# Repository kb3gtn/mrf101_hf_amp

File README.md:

# MRF101 HF AMP design

## Introduction
This repository contains multiple circuits board designs for a 100W HF Amp using a single MRF-101A transistor.   This design is based on a design by HF5L.   This design operates with a 48V Nominal supply at around 3.5 Amps of current.

Input match is good from 160M -> 6M band (1.8M -> 54 MHz).   Device has a between 16 -> 20 dB of gain depending on frequency.

## KICAD design files
The Main Amp Deck consists of the MRF101 transistor and input/output matching circuitry.
This can be found in the /Amp_Main_Deck/kicad folder in this repository.   The amplifier deck requires output filtering to remove odd harmonics produced by the Class AB amp.   The filters are selected per band of operation.

## Powering the Amp
The concept to power the amplifier design is to use 2 6S LiPo batteries in series.  This will provide a 44 -> 52v operating range.  Current plan is to use RC batteries and off the shelf chargers for portable operation.

## TODO
Design some BFP filters for each of the HF Amateur Radio bands, will need to develop a switch bank to select which filter should be in line.   Using BPF because this will provide some selectivity and limit the amount of bandwidth being sampled for a SDR receiver architecture.

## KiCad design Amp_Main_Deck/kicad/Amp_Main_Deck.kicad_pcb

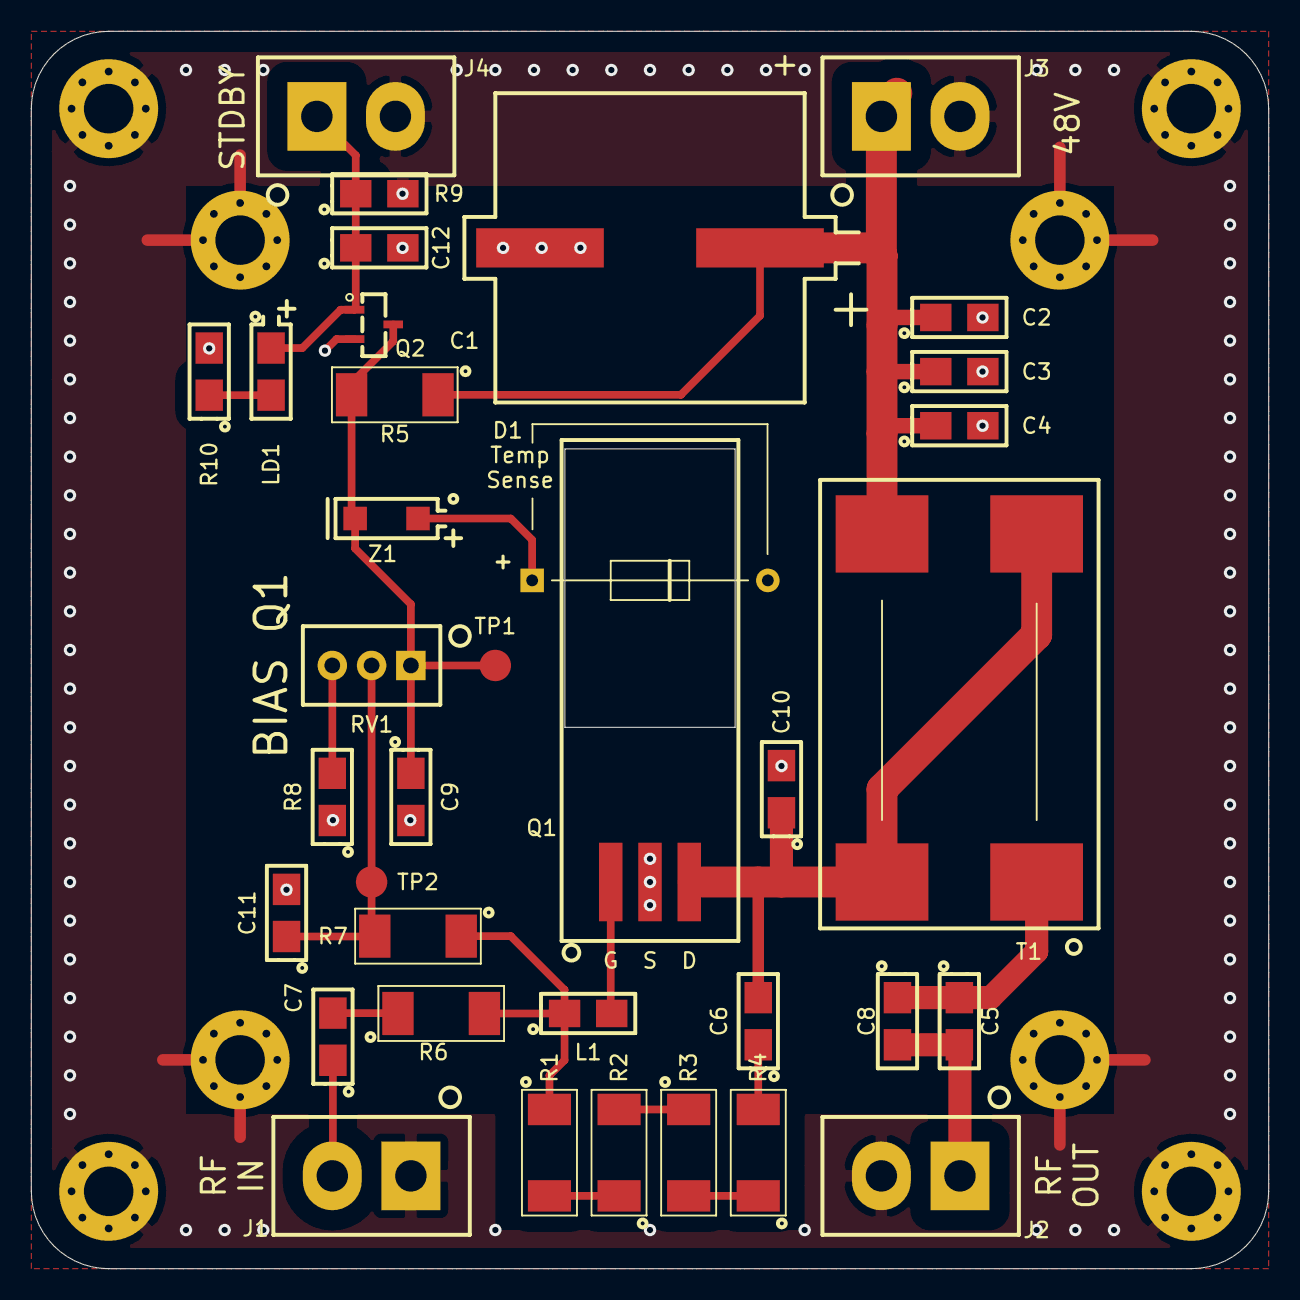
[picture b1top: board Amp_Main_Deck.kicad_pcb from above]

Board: 2 copper layers, 80.0 x 80.0 mm, 44 parts (0 on the bottom side), 19 nets.

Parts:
C1: CP; UCZ1K331MNQ1MS
C2, C3, C4, C5, C6, C7, C8, C9, C10, C11, C12: C; 0805_handsolder
D1: Diode_Generic; Diode_600mil
H1, H2, H3, H4, H5, H6, H7, H8: MountingHole_Pad; MountingHole_3.2mm_M3_Pad_Via
J1, J2, J3, J4: TermBlock_2pin; TermBlock_200mil_2pin
L1: L; 0805_handsolder
LD1: Diode_LED; 0805_handsolder_Pol
Q1: MRF101A; MRF-101AN_SM
Q2: 2N7002; SOT-23
R1, R2, R3, R4, R5, R6, R7: R; 2010_handsolder
R8, R9, R10: R; 0805_handsolder
RV1: Trim_POT; 3296W-1-103LF
T1: CMC; 744851330
TP1, TP2: SMD_TP
Z1: Diode_Zener; SOD123

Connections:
/48v: C1.1, C2.1, C3.1, C4.1, J3.1, R5.1, T1.3
/A: C7.1, J1.1
/B: C7.2, R6.1
/C: L1.1, R1.1, R6.2, R7.1
/E: L1.2, Q1.1
/MRF_DRAIN: C6.2, C10.1, Q1.3, T1.2, T1.4
/RF_OUT: C5.2, C8.2, J2.1
/T1_OUT: C5.1, C8.1, T1.1
/TEMP_SENSE: D1.1, Z1.1
/bias_ref: C9.1, Q2.2, R5.2, RV1.1, TP1.1, Z1.2
/bias_voltage: C11.1, R7.2, RV1.2, TP2.1
/standby: C12.1, J4.1, LD1.1, Q2.1, R9.1
GND: C1.2, C2.2, C3.2, C4.2, C9.2, C10.2, C11.2, C12.2, D1.2, H1.1, H2.1, H3.1, H4.1, H5.1, H6.1, H7.1, H8.1, J1.2, J2.2, J3.2, J4.2, Q1.2, Q2.3, R8.1, R9.2, R10.2
unnamed: C6.1, R4.2
unnamed: LD1.2, R10.1
unnamed: R1.2, R2.1
unnamed: R2.2, R3.1
unnamed: R3.2, R4.1
unnamed: R8.2, RV1.3

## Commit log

2021-02-07 Initial Checking of a working design on the bench.
2021-02-12 project library updated
    updated project files to include local libraries correctly
2021-02-12 project file tweak
2021-02-12 Add some documentation and inital testing setup.
